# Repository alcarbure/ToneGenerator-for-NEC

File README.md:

# ToneGenerator for NEC

[Project sample](AtWork/Images/Presentation.jpg)

Il s’agit de réaliser un petit générateur de son et d’ultrason afin de faire connaitre au public, le monde des chauve-souris lors des NEC ( nuit européenne des chauve-souris).

This involves creating a small sonic and ultrasonic generator in order to raise awareness of the world of bats during the NEC (European Bat Night).

_____________________________________________________________

## Projet initial : 
La première version du générateur de son/ultarson étais axée sur un NE555 bien connus de nos ancien dont je fais partie, mais le principal inconvénient est sa stabilité dans le temps ceci dû au composant utilisé pour la génération du signal rectangulaire analogique. De nombreux utilisateur se plaignais des erreurs de fréquence assez importante dû au vieillissement des résistances du contacteur rotatif et des condensateurs. 
## Project actuel : 
Etant donné le nombre de réparation qui m’étais demandé, j’ai décidé de mettre ce projet au gout du jour. Dès lors, J’ai basé ce nouvel opus sur un Arduino Pro-Mini (5V) qui lui restera suffisamment stable en fréquence grâce a son Xtal de 16Mhz et donc en faire aussi un appareil de calibrage pour les anciens détecteurs tel que les anciens Petterson ou de vérifier l’état de vos micro ultrasonique. J’ai donc gardé cette idée axée autour du contacteur rotatif (un potentiomètre linaire peut aussi faire l’affaire) avec une combinaison permettant d’atteindre une fréquence maximum de 32KHz, bien sur il faut que le HP piezo arrive à diffuser cette fréquence. 
Ce montage fonctionne sur une pile de 9V, mais peut-être facilement adapté pour une alimentation 12v en y ajoutant un régulateur AMS1117—5V (ensemble D1-IC1).

### Descriptif : 
L’ensemble est axé sur l’Arduino Pro Mini soudé sur un petit circuit imprimé que vous trouverais dans le dossier PCB-SMD. Il est possible de faire soi-même ce circuit en utilisant d’anciennes résistances plutôt que l’utilisation des composant de surface. Mais l’idée est de faire fabriquer l’ensemble de vos circuits par une société tel que JLCPCB qui propose le montage des composants SMD et de le tropicaliser plus facilement avec un vernis adéquat. Il faut compter à ce jour (2024) +/-24€ + port pour 20 pièces. Il vous restera à souder le contacteur rotatif, l’Arduino et quelque fils entre les autres composants du projet.
### PCB & Gerber
Dans le dossier **Dossier -JLCPCB** se trouve, les fichiers pour JLCPCB ou votre fabriquant favori,
Vous y trouverais aussi les fichiers Gerber, les fichier KidCad 7.xx ainsi que ses librairies et une version PDf de ces fichiers.

### AtWork
Ce dossier comprend la liste du matériel dont vous avez besoin, le plan de câblage, un exemple de plan d’assemblage du boitier en bois, le STL pour imprimer le support du circuit si vous ne voulez pas le coller au boitier et quelques images.
Imprimez ‘pannel.jpg’ et plastifiiez-le. Il sera la face supérieure sur laquelle sera fixé l’interrupteur et le commutateur rotatif à 12 positions 
### Software
Inutile de dire que le software se trouve dans ce dossier 😉

Je vous souhaite bien du plaisir pour réaliser ce petit projet cher au passionné des chauve-souris dont je fais partie dans le groupe des volontaire Plecotus de Natagora Belgique. 

___________________________________________________________________________________________________ 

## Initial project: 
The first version of the sonic/ultarsonic generator was based on a NE555 well known to our elders of which I am a part, but the main disadvantage is its stability over time, due to the component used for the generation of the analog rectangular signal. Many users complained of fairly large frequency errors due to the aging of the rotary contactor resistors and capacitors. 
## Current project: 
Given the number of repairs that were required of me, I decided to bring this project up to date. From then, I based this new opus on an Arduino Pro-Mini (5V) which will remain sufficiently stable in frequency wit Xtal 16Mhz inside and therefore also make it a calibration device for old detectors such as the old Petterson or check the condition of your ultrasonic microphone. I therefore kept this idea centered around the rotary contactor (a linear potentiometer can also used) with a combination allowing a maximum frequency of 32KHz to be reached, of course the piezo speaker must be able to diffuse this frequency. This assembly runs on a 9V battery, but can easily be adapted for a 12v power supply by adding an AMS1117—5V regulator (D1-IC1 set). 
### Description:
 The whole thing is focused on the Arduino Pro Mini soldered on a small printed circuit that you would find in the PCB-SMD folder. It is possible to make this circuit yourself using old resistors rather than using surface components. But the idea is to have all of your circuits manufactured by a company such as JLCPCB which offers the assembly of SMD components and to tropicalize it more easily with a suitable varnish. As of today (2024), you need to count +/-24€ + shipping for 20 pieces. You will still have to solder the rotary contactor, the Arduino and some wires between the other components of the project. 
### PCB & Gerber
In the floder **Dossier-JLCPCB** you will find the files for JLCPCB or your favorite manufacturer, You will also find Gerber files, KidCad 7.xx files as well as its libraries and a PDF version of these files. 
### AtWork
This file includes the list of materials you need, the wiring plan, an example of an assembly plan for the wooden case, the STL to print the circuit support if you do not want to glue it to the case and some images. 
Print ‘pannel.jpg’ and laminate it. It will be the upper face on which the switch and the 12-positions rotary switch will be fixed. 
 
###Software
Needless to say, the software is in this folder 😉
I wish you a lot of fun carrying out this little project dear to the bat enthusiast of which I am a part in the group of Plecotus volunteers from Natagora Belgium.

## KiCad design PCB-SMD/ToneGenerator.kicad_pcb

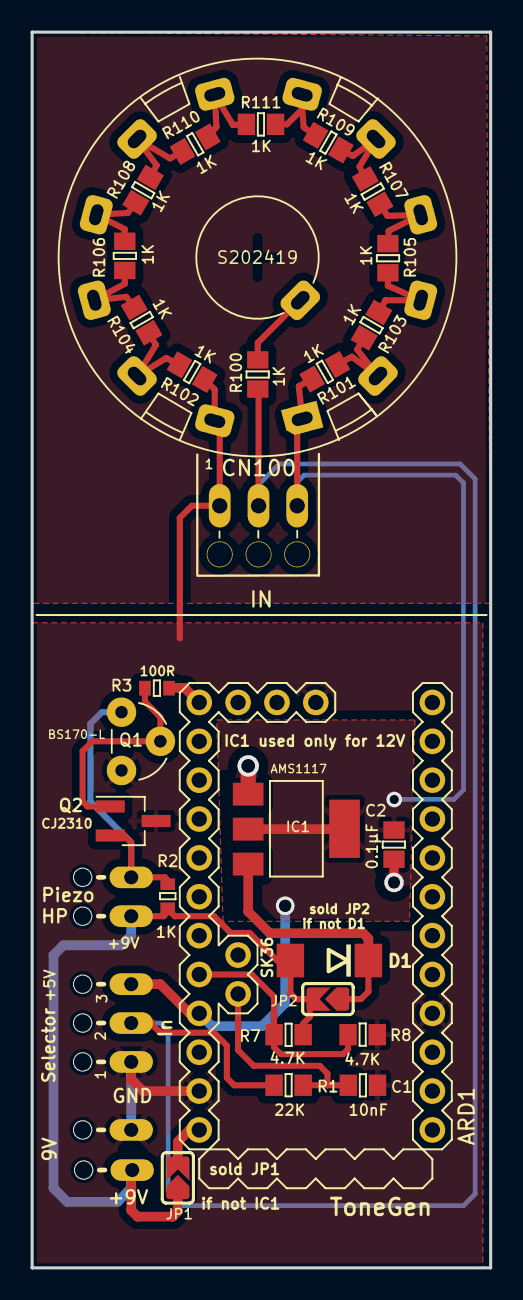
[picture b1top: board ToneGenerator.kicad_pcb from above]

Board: 2 copper layers, 30.0 x 80.8 mm, 35 parts (0 on the bottom side), 22 nets.

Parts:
+9V0: AMP-01; W1
ARD1: ARDUINO_PRO_MINI_LT-2; ARDUINO_PRO_MINI_V2_LT
C1: 10nF; 0805
C2: 0.1µF; 0805
CN100: IN; W3X
D1: SK36; DO214AA
GND0: AMP-01; W1
HP1, HP2: AMP-01; W1
IC1: AMS1117; SOT-223
J100: Con-Rotatif-1X12; RS26-1P12T
JP1, JP2: JP1-ARROW_NOPASTE; SOLDERJUMPER_ARROW_NOPASTE
Q1: BS170-L; SOT54E-L
Q2: CJ2310; SOT-23_Handsoldering
R1: 22K; 0805
R2: 1K; 0603
R3: 100R; 0603
R7, R8: 4.7K; 0805
R100, R101, R102, R103, R104, R105, R106, R107, R108, R109, R110, R111: 1K; 0805
S+0: AMP-01; W1
S-0: AMP-01; W1
SIN0: AMP-01; W1

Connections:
+5V: ARD1.VCC (VCC@2), C2.1, CN100.3, IC1.2 (VO), IC1.4 (VO1), J100.1, R101.1, S+0.1 (KL)
+9V: +9V0.1 (KL), D1.A, HP1.1 (KL), JP1.1, JP2.2, R2.2, R7.2
/SIN0: CN100.2, R1.2, R100.2, SIN0.1 (KL)
GND: ARD1.GND, ARD1.GND@1, ARD1.GND@4, C1.2, C2.2, CN100.1, GND0.1 (KL), IC1.3 (ADJ), J100.12, Q1.S, Q2.3 (S), R8.1, R102.1, S-0.1 (KL)
unnamed: ARD1.A3, R7.1, R8.2
unnamed: ARD1.A5, C1.1, R1.1
unnamed: ARD1.D10, R3.2
unnamed: ARD1.RAW, JP1.2
unnamed: D1.C (K), IC1.1 (VI), JP2.1
unnamed: HP2.1 (KL), Q1.D, Q2.2 (D), R2.1
unnamed: J100.2, R101.2, R103.1
unnamed: J100.3, R103.2, R105.1
unnamed: J100.4, R105.2, R107.1
unnamed: J100.5, R107.2, R109.1
unnamed: J100.6, R109.2, R111.2
unnamed: J100.7, R110.2, R111.1
unnamed: J100.8, R108.2, R110.1
unnamed: J100.9, R106.2, R108.1
unnamed: J100.10, R104.2, R106.1
unnamed: J100.11, R102.2, R104.1
unnamed: J100.A, R100.1
unnamed: Q1.G, Q2.1 (G), R3.1

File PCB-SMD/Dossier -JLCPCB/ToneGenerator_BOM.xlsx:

Item | Designator | Qty | Manufacturer | MFR.Part # | LCSC Part # | Description / Value | Footprint | Comment | Part
1 | C1 | 1 | Samsung Electro-Mechanics | CL21B103KBANNNC | C1710 | 50V 10nF X7R ±10% 0805 Multilayer Ceramic Capacitors MLCC - SMD/SMT ROHS | 0805 |  | Basic
2 | C2 | 1 | YAGEO | CC0805KRX7R9BB104 | C49678 | 50V 100nF X7R ±10% 0805 Multilayer Ceramic Capacitors MLCC - SMD/SMT ROHS | 0805 |  | Basic
3 | R1 | 1 | UNI-ROYAL(Uniroyal Elec) | 0805W8F2202T5E | C17560 | 125mW Thick Film Resistors 150V ±100ppm/℃ ±1% 22kΩ 0805 Chip Resistor - Surface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 | 0805 |  | Basic
4 | R2 | 1 | UNI-ROYAL(Uniroyal Elec) | 0603WAF1001T5E | C21190 | 100mW Thick Film Resistors 75V ±100ppm/℃ ±1% 1kΩ 0603 Chip Resistor - Surface M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 | 0603 |  | Basic
5 | R3 | 1 | UNI-ROYAL(Uniroyal Elec) | 0603WAF1000T5E | C22775 | 100mW Thick Film Resistors 75V ±1% ±200ppm/℃ 100Ω 0603 Chip Resistor - Surface 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 | 0603 |  | Basic
6 | R7 | 1 | UNI-ROYAL(Uniroyal Elec) | 0805W8F4701T5E | C17673 | 125mW Thick Film Resistors 150V ±100ppm/℃ ±1% 4.7kΩ 0805 Chip Resistor - Surfac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 | 0805 |  | Basic
7 | R8 | 1 | UNI-ROYAL(Uniroyal Elec) | 0805W8F4701T5E | C17673 | 125mW Thick Film Resistors 150V ±100ppm/℃ ±1% 4.7kΩ 0805 Chip Resistor - Surfac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 | 0805 |  | Basic
8 | R100,R108,R102,R105, R101,R106,R109,R107, R104,R103,R111,R110 | 12 | UNI-ROYAL(Uniroyal Elec) | 0805W8F1001T5E | C17513 | 125mW Thick Film Resistors 150V ±100ppm/℃ ±1% 1kΩ 0805 Chip Resistor - Surface 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 | 0805 |  | Basic
9 | Q2 | 1 | Jiangsu Changjing Electronics Technology Co., Ltd. | CJ2310 | C75882 | 60V 3A 105mΩ@10V,3A 350mW 2V 1PCSNChannel SOT-23 MOSFETs ROHS | SOT-23 |  | Extended

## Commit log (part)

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2024-06-03 Ajout d’informations sur la finalité du projet
2024-06-03 Project Picture
2024-06-03 Project Update
2024-06-04 Upadte site
2024-06-05 Last Update
2024-06-26 PCB Update
2024-06-26 Update hardware
2024-07-02 Box update
2024-07-15 Update Wood box
2024-07-18 global update
